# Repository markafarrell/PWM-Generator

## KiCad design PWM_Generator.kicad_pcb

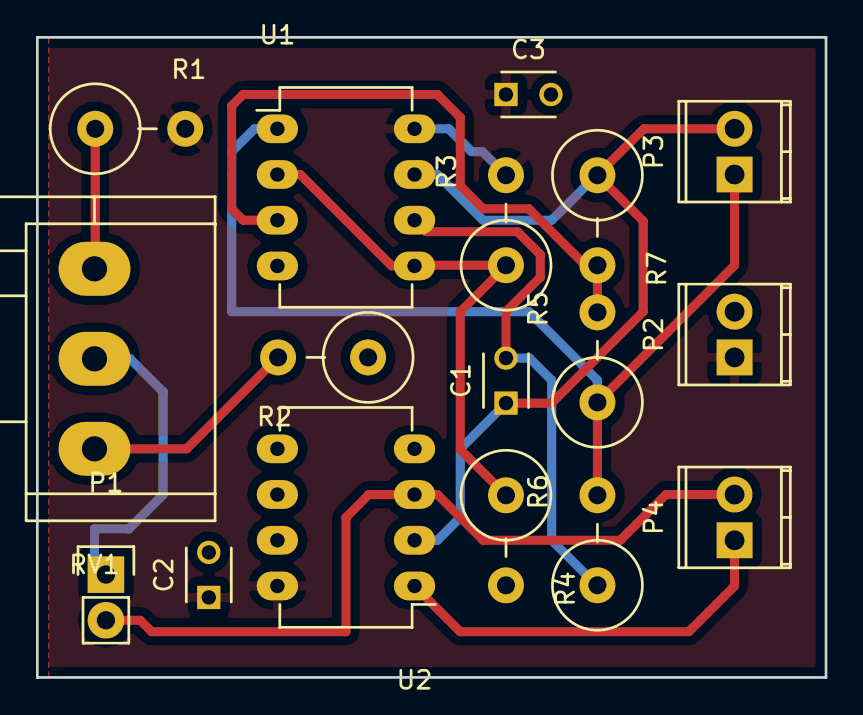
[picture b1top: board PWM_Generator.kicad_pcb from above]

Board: 2 copper layers, 43.8 x 35.6 mm, 17 parts (0 on the bottom side), 12 nets.

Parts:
C1: 100nF; C_Disc_D3_P2.5
C2, C3: 100n; C_Disc_D3_P2.5
P1: CONN_01X02; Pin_Header_Straight_1x02
P2, P3, P4: CONN_01X02; TerminalBlock_Pheonix_MPT-2.54mm_2pol
R1, R2: 10k; Resistor_Vertical_RM5mm
R3: 330k; Resistor_Vertical_RM5mm
R4: 220k; Resistor_Vertical_RM5mm
R5, R6: 1k; Resistor_Vertical_RM5mm
R7: 470; Resistor_Vertical_RM5mm
RV1: 100k; Potentiometer_Alps-RK16-single_largePads
U1, U2: LM358N; DIP-8_W7.62mm_LongPads

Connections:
/PWM: P4.1, U2.1
/Square: P3.1, R5.1, R6.2, U1.1
/Triange: C1.1, P3.2, R7.1, U1.7, U2.2
/Vctrl: P1.2, P4.2, U2.3
/Vctrl_pot: P1.1, RV1.2
/Vref: R3.1, R4.1, U1.2, U1.5
GND: C2.2, C3.2, P2.2, R2.1, R4.2, U1.4, U2.4
unnamed: C1.2, R6.1, U1.6
unnamed: R1.1, RV1.3
unnamed: R2.2, RV1.1
unnamed: R5.2, R7.2, U1.3
VCC: C2.1, C3.1, P2.1, R1.2, R3.2, U1.8, U2.8

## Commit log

2016-07-03 :octocat: Added .gitattributes & .gitignore files
